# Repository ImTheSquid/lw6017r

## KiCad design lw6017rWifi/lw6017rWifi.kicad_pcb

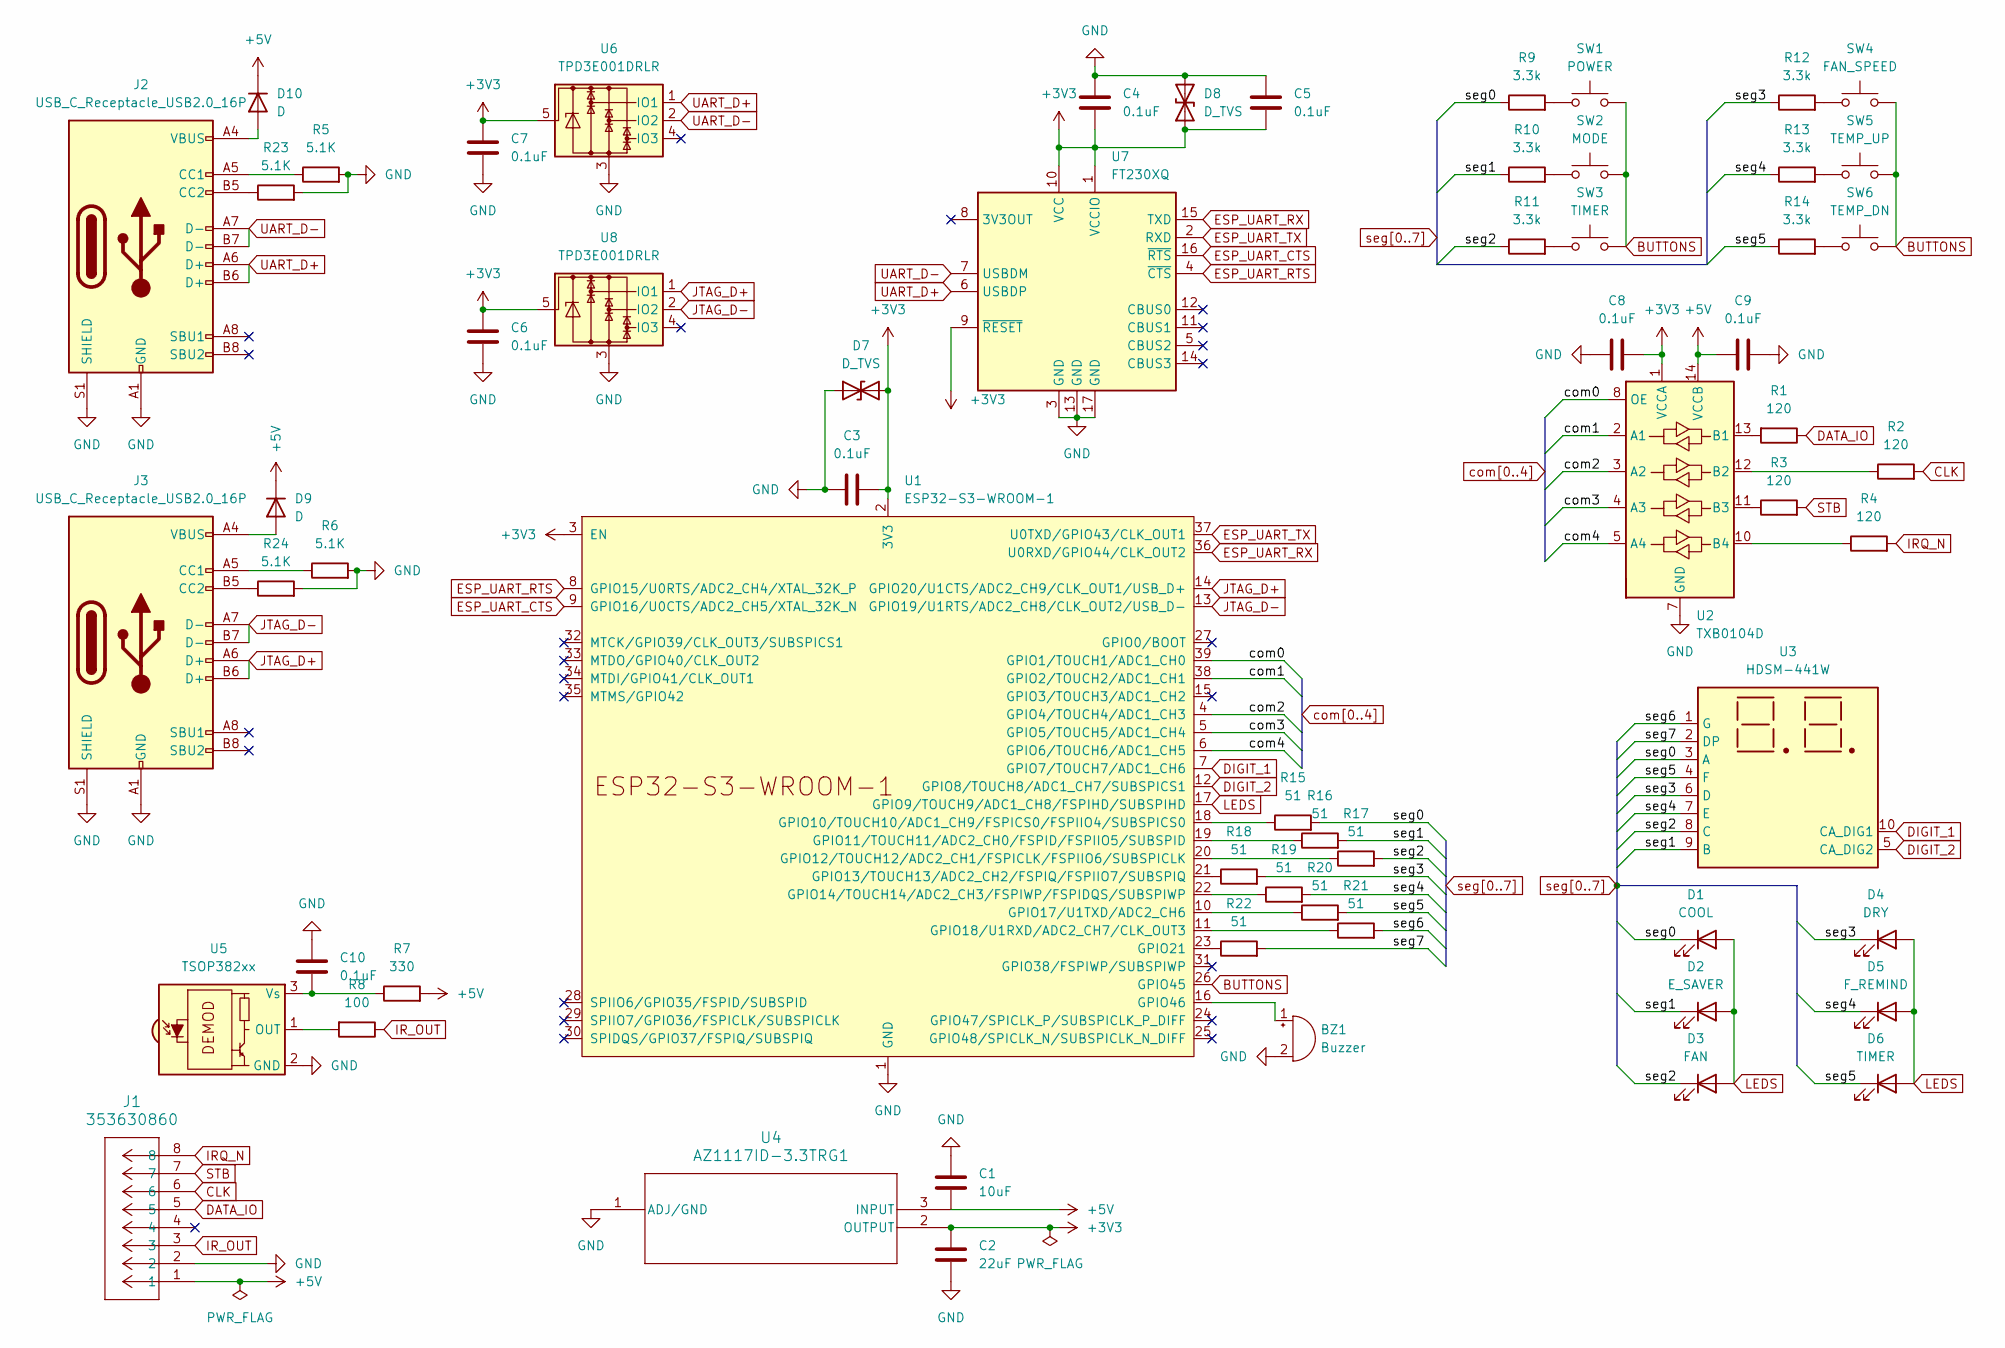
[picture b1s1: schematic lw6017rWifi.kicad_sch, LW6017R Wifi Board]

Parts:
BZ1: Buzzer; Buzzer_12x9.5RM7.6
C1: 10uF; C_0805_2012Metric
C2: 22uF; C_0805_2012Metric
C3, C4, C5, C6, C7, C8, C9, C10: 0.1uF; C_0402_1005Metric
D1: COOL; LED_D5.0mm
D2: E_SAVER; LED_D5.0mm
D3: FAN; LED_D5.0mm
D4: DRY; LED_D5.0mm
D5: F_REMIND; LED_D5.0mm
D6: TIMER; LED_D5.0mm
D7, D8: D_TVS; D_SOD-882; LCSC C500765
D9, D10: D; D_SOD-323; LCSC C78740
J1: 353630860; CON_353630860
J2, J3: USB_C_Receptacle_USB2.0_16P; USB_C_Receptacle_GCT_USB4105-xx-A_16P_TopMnt_Horizontal; LCSC C2835315
R1, R2, R3, R4: 120; R_0402_1005Metric
R5, R6, R23, R24: 5.1K; R_0402_1005Metric
R7: 330; R_0402_1005Metric
R8: 100; R_0402_1005Metric
R9, R10, R11, R12, R13, R14: 3.3k; R_0402_1005Metric
R15, R16, R17, R18, R19, R20, R21, R22: 51; R_0402_1005Metric
SW1: POWER; SW_PUSH_6mm
SW2: MODE; SW_PUSH_6mm
SW3: TIMER; SW_PUSH_6mm
SW4: FAN_SPEED; SW_PUSH_6mm
SW5: TEMP_UP; SW_PUSH_6mm
SW6: TEMP_DN; SW_PUSH_6mm
U1: ESP32-S3-WROOM-1; LCSC C2980296
U2: TXB0104D; SOIC-14_3.9x8.7mm_P1.27mm; LCSC C1549752
U3: HDSM-441W; HDSM-441B_HDSM-443B
U4: AZ1117ID-3.3TRG1; TO-252-2; LCSC C2926306
U5: TSOP382xx; Vishay_MINICAST-3Pin
U6, U8: TPD3E001DRLR; SOT-553; LCSC C470828
U7: FT230XQ; QFN-16-1EP_4x4mm_P0.65mm_EP2.1x2.1mm; LCSC C128629

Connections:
+3V3: C2.1, C3.1, C4.1, C5.1, C6.1, C7.1, C8.1, D7.2 (A2), D8.1 (A1), U1.2 (3V3), U1.3 (EN), U2.1 (VCCA), U4.2 (OUTPUT), U6.5, U7.1 (VCCIO), U7.9 (~RESET), U7.10 (VCC), U8.5
+5V: C1.1, C9.2, D9.1 (K), D10.1 (K), J1.1, R7.2, U2.14 (VCCB), U4.3 (INPUT)
BUTTONS: SW1.2, SW2.2, SW3.2, SW4.2, SW5.2, SW6.2, U1.26 (GPIO45)
CLK: J1.6, R2.2
DATA_IO: J1.5, R1.1
DIGIT_1: U1.7 (GPIO7/TOUCH7/ADC1_CH6), U3.10 (CA_DIG1)
DIGIT_2: U1.12 (GPIO8/TOUCH8/ADC1_CH7/SUBSPICS1), U3.5 (CA_DIG2)
ESP_UART_CTS: U1.9 (GPIO16/U0CTS/ADC2_CH5/XTAL_32K_N), U7.16 (~RTS)
ESP_UART_RTS: U1.8 (GPIO15/U0RTS/ADC2_CH4/XTAL_32K_P), U7.4 (~CTS)
ESP_UART_RX: U1.36 (U0RXD/GPIO44/CLK_OUT2), U7.15 (TXD)
ESP_UART_TX: U1.37 (U0TXD/GPIO43/CLK_OUT1), U7.2 (RXD)
GND: BZ1.2 (-), C1.2, C2.2, C3.2, C4.2, C5.2, C6.2, C7.2, C8.2, C9.1, C10.2, D7.1 (A1), D8.2 (A2), J1.2, J2.A1 (GND), J2.A12 (GND), J2.B1 (GND), J2.B12 (GND), J2.S1 (SHIELD), J3.A1 (GND), J3.A12 (GND), J3.B1 (GND), J3.B12 (GND), J3.S1 (SHIELD), R5.2, R6.2, R23.2, R24.2, U1.1 (GND), U1.40 (GND), U1.41 (GND), U2.7 (GND), U4.1 (ADJ/GND), U5.2 (GND), U6.3, U7.3 (GND), U7.13 (GND), U7.17 (GND), U8.3
IRQ_N: J1.8, R4.2
IR_OUT: J1.3, R8.1
JTAG_D+: J3.A6 (D+), J3.B6 (D+), U1.14 (GPIO20/U1CTS/ADC2_CH9/CLK_OUT1/USB_D+), U8.1 (IO1)
JTAG_D-: J3.A7 (D-), J3.B7 (D-), U1.13 (GPIO19/U1RTS/ADC2_CH8/CLK_OUT2/USB_D-), U8.2 (IO2)
LEDS: D1.2 (A), D2.2 (A), D3.2 (A), D4.2 (A), D5.2 (A), D6.2 (A), U1.17 (GPIO9/TOUCH9/ADC1_CH8/FSPIHD/SUBSPIHD)
unnamed: BZ1.1 (+), U1.16 (GPIO46)
unnamed: D9.2 (A), J3.A4 (VBUS), J3.A9 (VBUS), J3.B4 (VBUS), J3.B9 (VBUS)
unnamed: D10.2 (A), J2.A4 (VBUS), J2.A9 (VBUS), J2.B4 (VBUS), J2.B9 (VBUS)
unnamed: J2.A5 (CC1), R5.1
unnamed: J2.B5 (CC2), R23.1
unnamed: J3.A5 (CC1), R6.1
unnamed: J3.B5 (CC2), R24.1
unnamed: R9.2, SW1.1
unnamed: R10.2, SW2.1
unnamed: R11.2, SW3.1
unnamed: R12.2, SW4.1
unnamed: R13.2, SW5.1
unnamed: R14.2, SW6.1
unnamed: R15.1, U1.18 (GPIO10/TOUCH10/ADC1_CH9/FSPICS0/FSPIIO4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)
unnamed: R16.1, U1.19 (GPIO11/TOUCH11/ADC2_CH0/FSPID/FSPIIO5/S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)
unnamed: R17.1, U1.20 (GPIO12/TOUCH12/ADC2_CH1/FSPICLK/FSPIIO6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)
unnamed: R18.1, U1.21 (GPIO13/TOUCH13/ADC2_CH2/FSPIQ/FSPIIO7/S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)
unnamed: R19.1, U1.22 (GPIO14/TOUCH14/ADC2_CH3/FSPIWP/FSPIDQS/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)
unnamed: R20.1, U1.10 (GPIO17/U1TXD/ADC2_CH6)
unnamed: R21.1, U1.11 (GPIO18/U1RXD/ADC2_CH7/CLK_OUT3)
unnamed: R22.1, U1.23 (GPIO21)
unnamed: R1.2, U2.13 (B1)
unnamed: R2.1, U2.12 (B2)
unnamed: R3.1, U2.11 (B3)
unnamed: R4.1, U2.10 (B4)
unnamed: R8.2, U5.1 (OUT)
unnamed: C10.1, R7.1, U5.3 (Vs)
STB: J1.7, R3.2
UART_D+: J2.A6 (D+), J2.B6 (D+), U6.1 (IO1), U7.6 (USBDP)
UART_D-: J2.A7 (D-), J2.B7 (D-), U6.2 (IO2), U7.7 (USBDM)
com0: U1.39 (GPIO1/TOUCH1/ADC1_CH0), U2.8 (OE)
com1: U1.38 (GPIO2/TOUCH2/ADC1_CH1), U2.2 (A1)
com2: U1.4 (GPIO4/TOUCH4/ADC1_CH3), U2.3 (A2)
com3: U1.5 (GPIO5/TOUCH5/ADC1_CH4), U2.4 (A3)
com4: U1.6 (GPIO6/TOUCH6/ADC1_CH5), U2.5 (A4)
seg0: D1.1 (K), R9.1, R15.2, U3.3 (A)
seg1: D2.1 (K), R10.1, R16.2, U3.9 (B)
seg2: D3.1 (K), R11.1, R17.2, U3.8 (C)
seg3: D4.1 (K), R12.1, R18.2, U3.6 (D)
seg4: D5.1 (K), R13.1, R19.2, U3.7 (E)
seg5: D6.1 (K), R14.1, R20.2, U3.4 (F)
seg6: R21.2, U3.1 (G)
seg7: R22.2, U3.2 (DP)

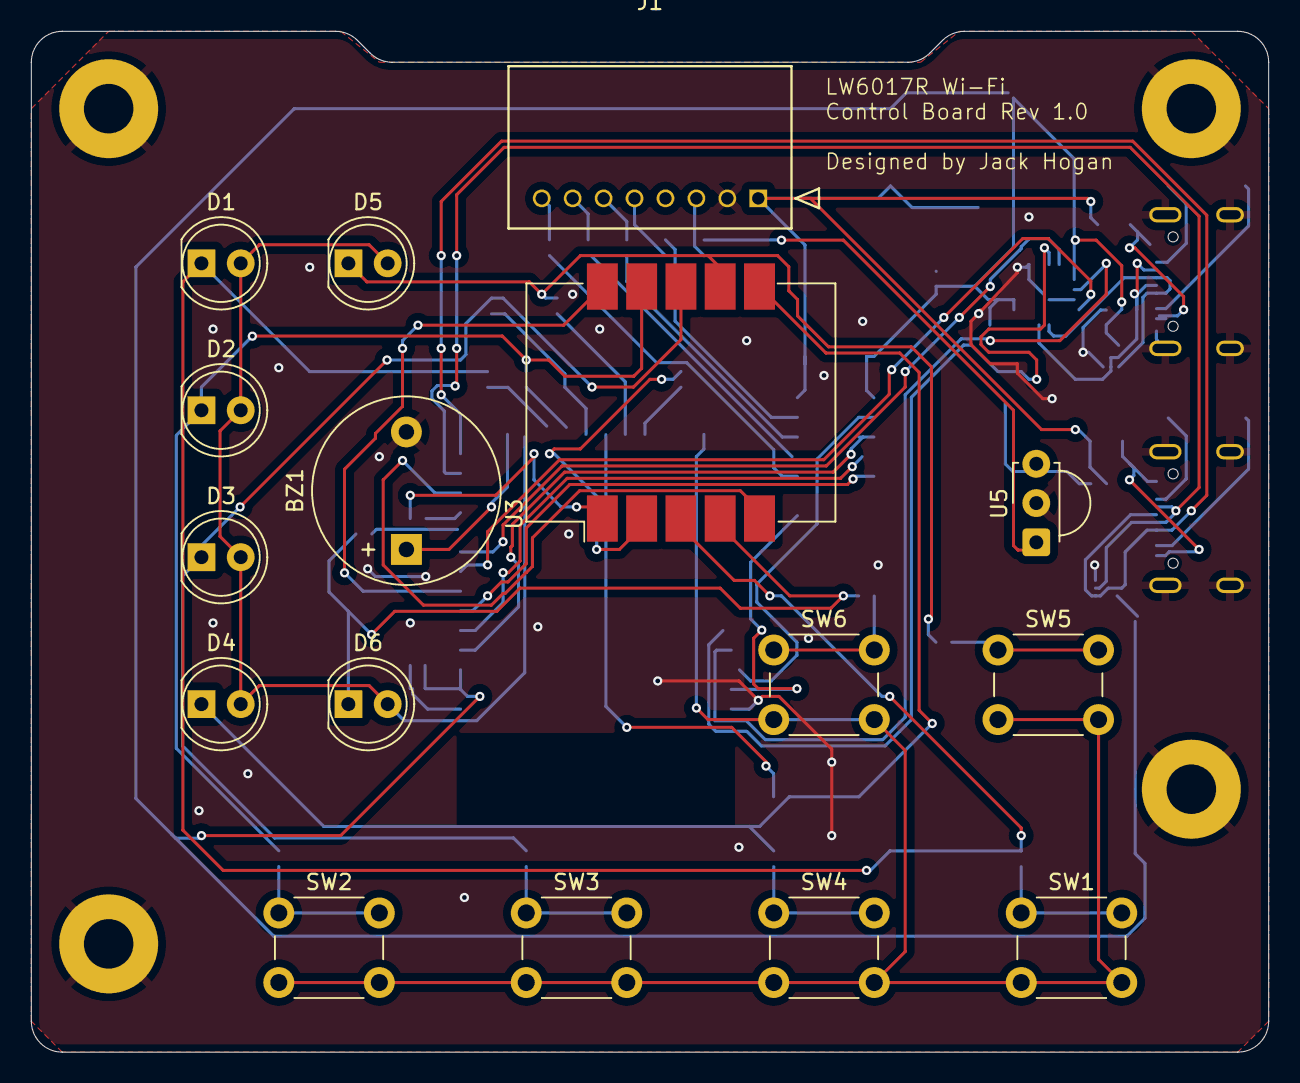
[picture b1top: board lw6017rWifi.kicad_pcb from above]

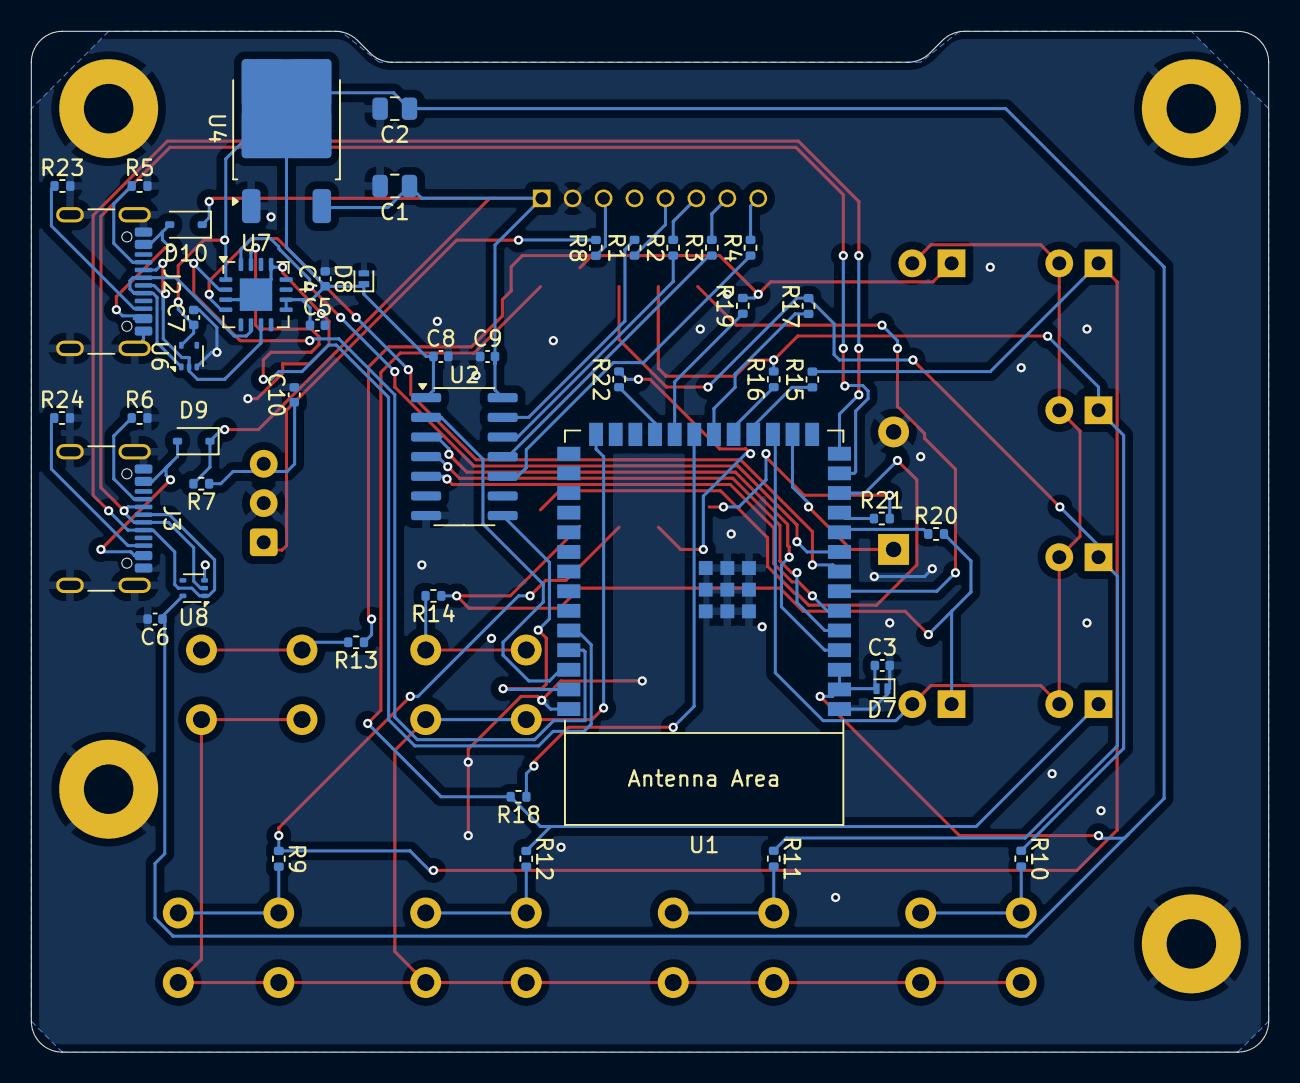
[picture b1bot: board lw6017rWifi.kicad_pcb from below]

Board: 2 copper layers, 80.0 x 66.0 mm, 62 parts (46 on the bottom side), 60 nets.

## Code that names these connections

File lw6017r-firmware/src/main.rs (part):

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    cpu_control::{CpuControl, Stack},
    delay::Delay,
    gpio::{
        AnyFlex, Event, Flex, Gpio10, Gpio11, Gpio12, Gpio13, Gpio14, Gpio17, Gpio18, Gpio2,
        Gpio21, Gpio4, Gpio45, Gpio5, Gpio6, Gpio7, Gpio8, Gpio9, Input, Io, Level, Output, Pull,
    },
    peripherals::Peripherals,
    prelude::*,
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
#[link_section = ".iram1"]
fn main_comms(
    stb: Input<'static, Gpio5>,
    clk: Input<'static, Gpio4>,
    mut data: Flex<'static, Gpio2>,
) -> ! {
    let mut buttons = 0_u32;
    'forever: loop {
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    let io = Io::new(peripherals.GPIO, peripherals.IO_MUX);

    // Setup data lines
    let stb = Input::new(io.pins.gpio5, Pull::Up);
    let data = Flex::new(io.pins.gpio2);

    let clk = Input::new(io.pins.gpio4, Pull::Up);
    let mut irq_n = Output::new(io.pins.gpio6, Level::High);

    // Setup buttons
    let mut buttons = Flex::new(io.pins.gpio45);

    // Setup segments
    let mut digit1 = Output::new(io.pins.gpio7, Level::Low);
    let mut digit2 = Output::new(io.pins.gpio8, Level::Low);
    let mut leds = Output::new(io.pins.gpio9, Level::Low);
    let mut segments = Segments {
        seg0: AnyFlex::new(io.pins.gpio10),
        seg1: AnyFlex::new(io.pins.gpio11),
        seg2: AnyFlex::new(io.pins.gpio12),
        seg3: AnyFlex::new(io.pins.gpio13),
        seg4: AnyFlex::new(io.pins.gpio14),
        seg5: AnyFlex::new(io.pins.gpio17),
        seg6: AnyFlex::new(io.pins.gpio18),
        seg7: AnyFlex::new(io.pins.gpio21),
    };

    let mut state = State {
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        // });

        log::info!("Starting comm thread");
        let _comm_enable = Output::new(io.pins.gpio1, Level::High);
        main_comms(stb, clk, data);
    });

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
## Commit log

2024-07-20 Worked on thread messaging and external comms
2024-07-20 More parsing work
2024-07-20 More code work
2024-07-20 Partially fixed read command
2024-07-20 More fixes
2024-07-21 More stuff
2024-07-21 Fixed some parsing
2024-07-24 More junk
2024-07-24 No lock
